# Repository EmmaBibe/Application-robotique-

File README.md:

# RoboMaster

Un parcours complet pour apprendre la robotique en partant de zéro, jusqu'au niveau attendu en Master, et au-delà.

L'idée : on ne mémorise pas une notion avant de l'avoir manipulée. Chaque leçon montre le phénomène de la source jusqu'au résultat (du courant dans un fil jusqu'au robot qui tourne), puis propose des simulateurs à manipuler, des quiz, des exercices corrigés, du code à écrire et des défis.

Fonctionne sur ordinateur et sur téléphone, s'installe comme une application et marche hors connexion. Aucun compte, aucune donnée envoyée : la progression reste sur l'appareil.

## Contenu

- **94 leçons** réparties en **28 modules** et **6 phases** :
  1. *Fondations* : bien démarrer, mathématiques, physique, électronique, programmation
  2. *Le cœur de la robotique* : mécanique et actionneurs, systèmes embarqués, robots mobiles, bras manipulateurs, commande et asservissements
  3. *Le robot intelligent* : perception et capteurs, vision, localisation et SLAM, planification, intelligence artificielle, ROS 2
  4. *L'ingénieur de demain* : ingénierie système et sécurité, créativité et invention, robotique de demain
  5. *Les frontières* : dynamique des robots, équilibre et robots à pattes, drones, essaims et multi-robots, optimisation et commande prédictive, interaction humain-robot, robotique molle et bio-inspirée
  6. *Objectif Mars* : une campagne de 13 missions qui croisent tous les domaines (fusée, trajectoire, atterrissage, énergie, rover, autonomie, terrain, hélicoptère, grottes, construction, ressources locales, dossier final), suivie de 3 ateliers « retour sur Terre » ancrés en RDC
- **29 simulateurs interactifs** : vecteurs, cercle trigonométrique, matrices de transformation, profil de mouvement, masse-ressort, engrenages, loi d'Ohm, PWM et pont en H, conversion analogique-numérique, robot différentiel et odométrie, bras 2 axes (modèles direct et inverse), PID, capteurs de distance (lidar, ultrason, infrarouge), filtrage et Kalman, filtre particulaire, A* et compagnie, convolution d'images, neurone artificiel, Q-learning, suiveur de ligne programmable, graphe ROS 2, dynamique d'un bras (Terre, Mars, Lune), pendule inversé (PID contre LQR), drone sur Terre et sur Mars, essaim d'exploration, transfert Terre-Mars, atterrissage propulsé, rover piloté avec délai radio, budget énergétique martien
- **Ateliers de conception** chiffrés (fusée à deux étages, mobilité d'un rover, énergie d'une base, drone de livraison, robot solaire) et **dossiers d'ingénieur** à questions ouvertes avec grille d'auto-évaluation, gardés dans le carnet
- **52 exercices de code** corrigés automatiquement, des dizaines d'exercices numériques et de quiz
- **Défis** : réglages de PID, choix de résistance, labyrinthe qui piège A*, tour chronométré du suiveur de ligne, et des défis créatifs à réaliser hors de l'écran
- **Révision espacée** (boîtes de Leitner) avec plus de 300 cartes
- **Carnet d'ingénieur** pour noter idées (problème, idée, prototype, test) et réflexions, exportable
- **Projets réels** avec matériel, budget et étapes : veilleuse, suiveur de ligne, bras à servos, gyropode, robot autonome sous ROS 2
- **Guide du Master** : programme type, outils à maîtriser, calendrier conseillé, stage et débouchés
- Glossaire français-anglais, recherche globale, minuteur de concentration, niveaux, badges, série de jours, thème clair et sombre

## Lancer l'application

Aucune dépendance, aucune étape de compilation. Il suffit de servir le dossier avec n'importe quel serveur web statique :

```bash
python3 -m http.server 8000
# puis ouvrir http://localhost:8000
```

Le mode hors ligne et l'installation nécessitent HTTPS (ou `localhost`). Pour publier, GitHub Pages, Netlify ou n'importe quel hébergement statique conviennent.

**Installer sur téléphone** : ouvrir le site, puis « Ajouter à l'écran d'accueil » dans le menu du navigateur.
**Installer sur ordinateur** : icône d'installation dans la barre d'adresse (Chrome, Edge).

**Changer d'appareil** : Profil → Exporter ma progression, puis Importer sur l'autre appareil.

## Organisation du code

```
index.html              coquille de l'application
css/app.css             styles (thème sombre et clair, mobile et bureau)
js/app.js               routeur et pages (accueil, parcours, leçon, labo, révision...)
js/core/                stockage local, gamification, interface, outils de dessin
js/views/blocks.js      rendu des blocs de leçon (quiz, exercices, code, défis...)
js/sims/                un fichier par simulateur, chargé à la demande
js/content/             le contenu pédagogique (un fichier par groupe de modules)
tools/build-sw.mjs      régénère sw.js (liste des fichiers mis en cache hors ligne)
```

### Ajouter ou modifier une leçon

Les leçons sont écrites dans `js/content/m-*.js` avec de petites fonctions (`P`, `H`, `Sim`, `Q`, `Exo`, `Code`, `Defi`...) définies dans `js/content/b.js`. Exemple :

```js
Q('q1', 'Que mesure un codeur ?', ['Une distance', 'Une rotation', 'Une température'], 1, 'Il compte les pas de rotation d\'un axe.'),
Exo('e1', 'Convertis 90° en radians.', { answer: 1.5708, tol: 0.001, sol: 'π/2 ≈ 1,571 rad' }),
Sim('pid', { Kp: 2 }),
```

Après toute modification, régénérer la liste du cache hors ligne :

```bash
node tools/build-sw.mjs
```

## Application Android (APK)

Le dossier `android/` contient une coquille Android minimale qui embarque l'application web et la fait tourner hors connexion. Pour reconstruire l'APK :

```bash
export ANDROID_HOME=/chemin/vers/android-sdk   # avec platforms;android-34 et build-tools;35.0.0
./android/build-apk.sh                         # produit android/RoboMaster.apk
```

Le script n'utilise ni Gradle ni Android Studio : aapt2, javac, d8, zipalign et apksigner suffisent. La clé `android/robomaster.keystore` sert uniquement aux versions de test ; elle est conservée pour que chaque nouvelle APK s'installe par-dessus la précédente sans perdre la progression.

## Application Windows

Le dossier `desktop/` contient une version de bureau basée sur Electron : une fenêtre qui sert l'application embarquée, sans installation ni connexion. Pour la reconstruire :

```bash
./desktop/build-windows.sh   # produit desktop/dist/RoboMaster-Windows.zip
```

Décompresser l'archive puis lancer `RoboMaster.exe`. La progression est enregistrée dans le profil Windows de l'utilisateur.

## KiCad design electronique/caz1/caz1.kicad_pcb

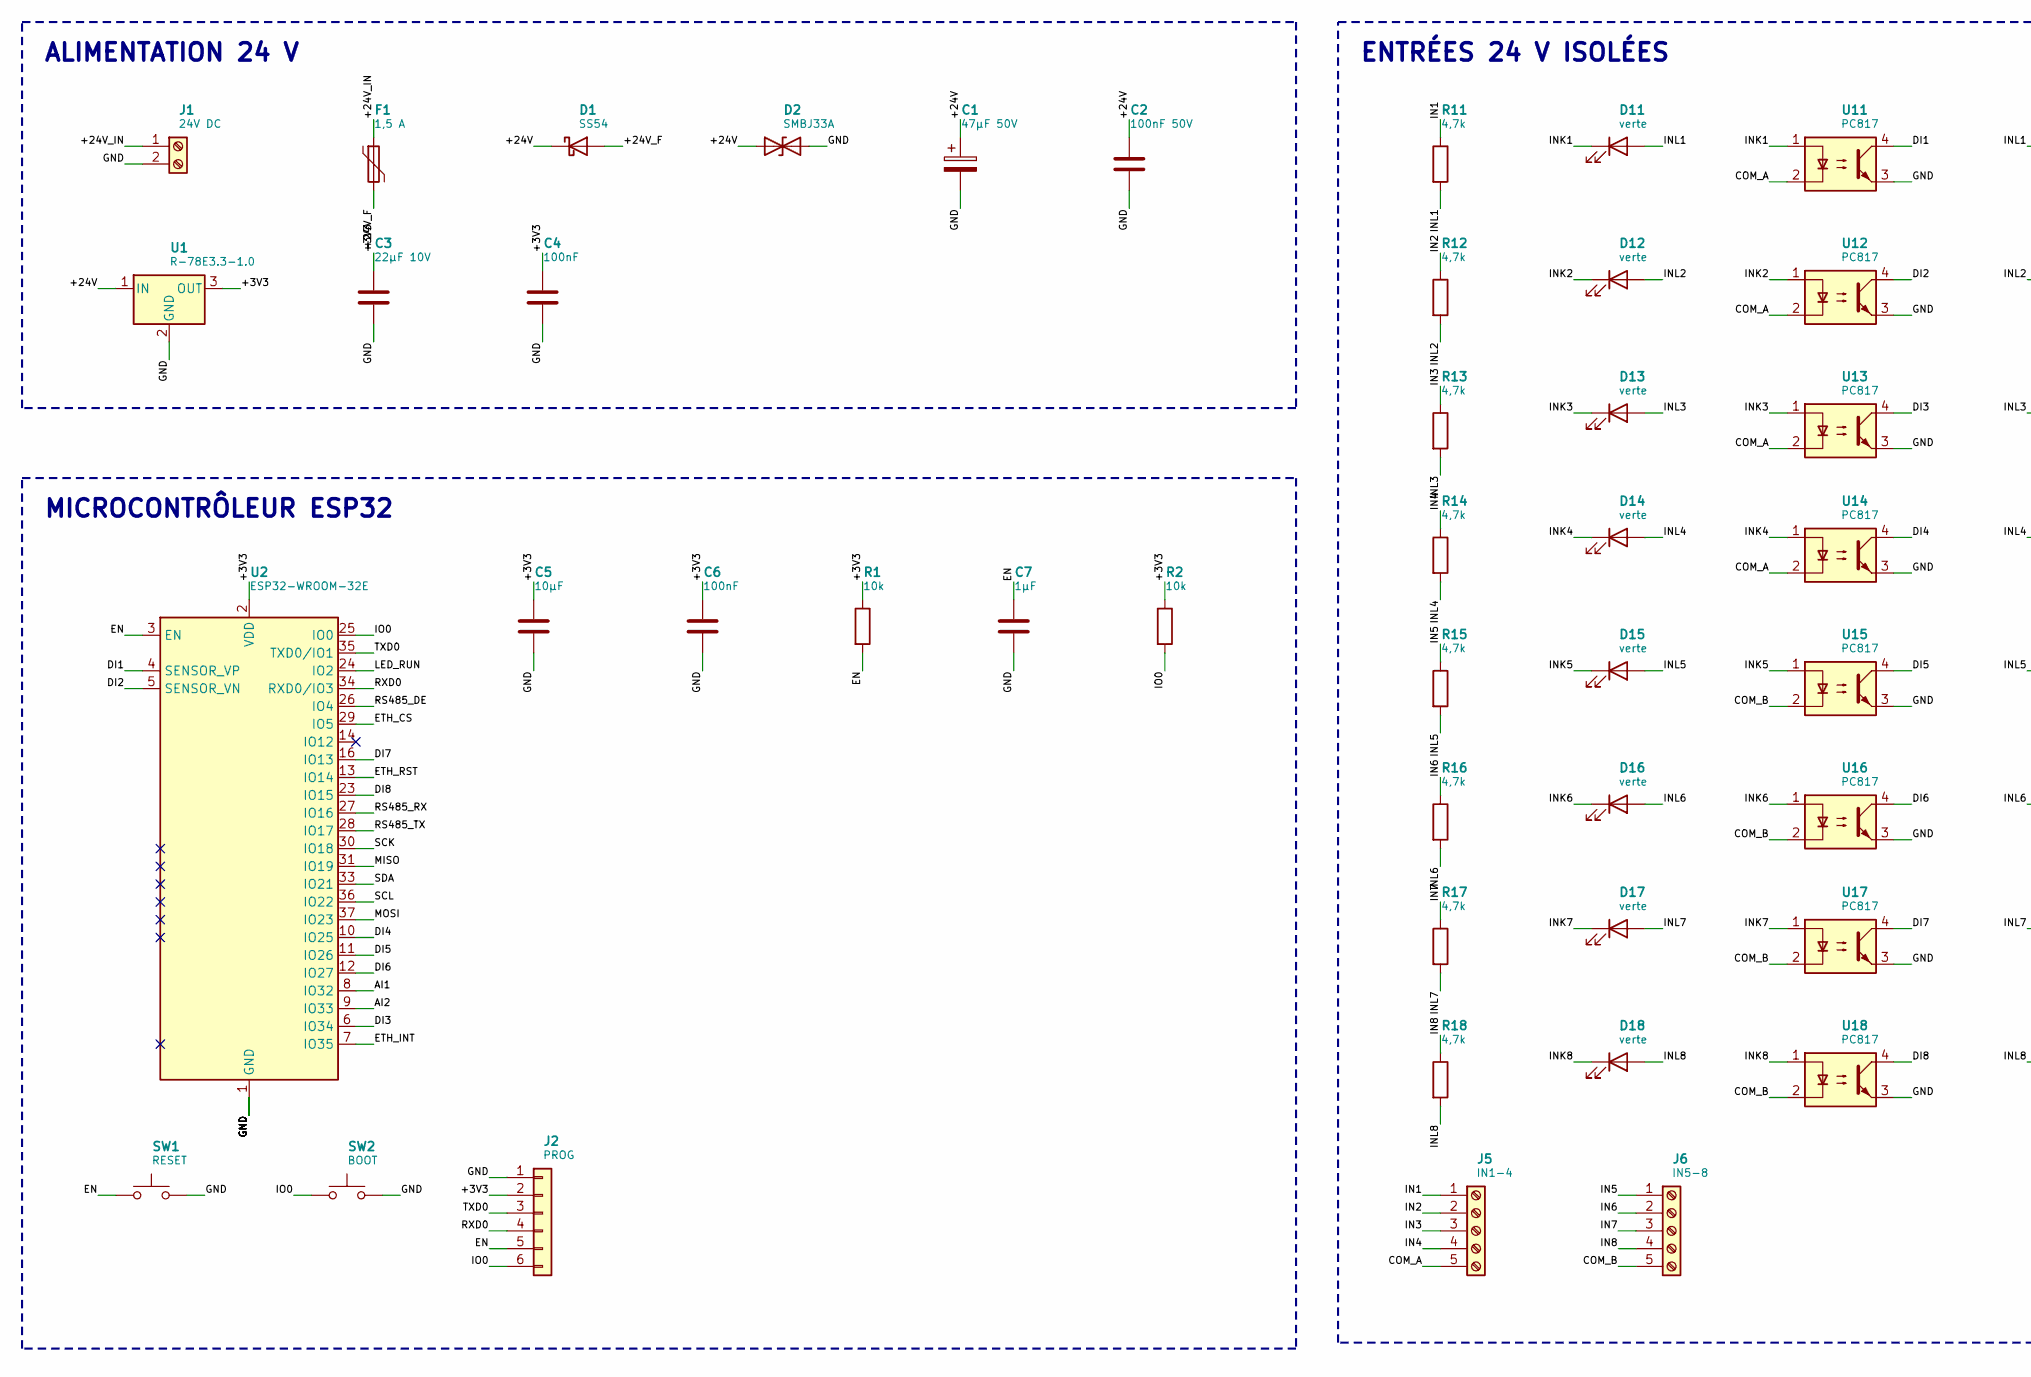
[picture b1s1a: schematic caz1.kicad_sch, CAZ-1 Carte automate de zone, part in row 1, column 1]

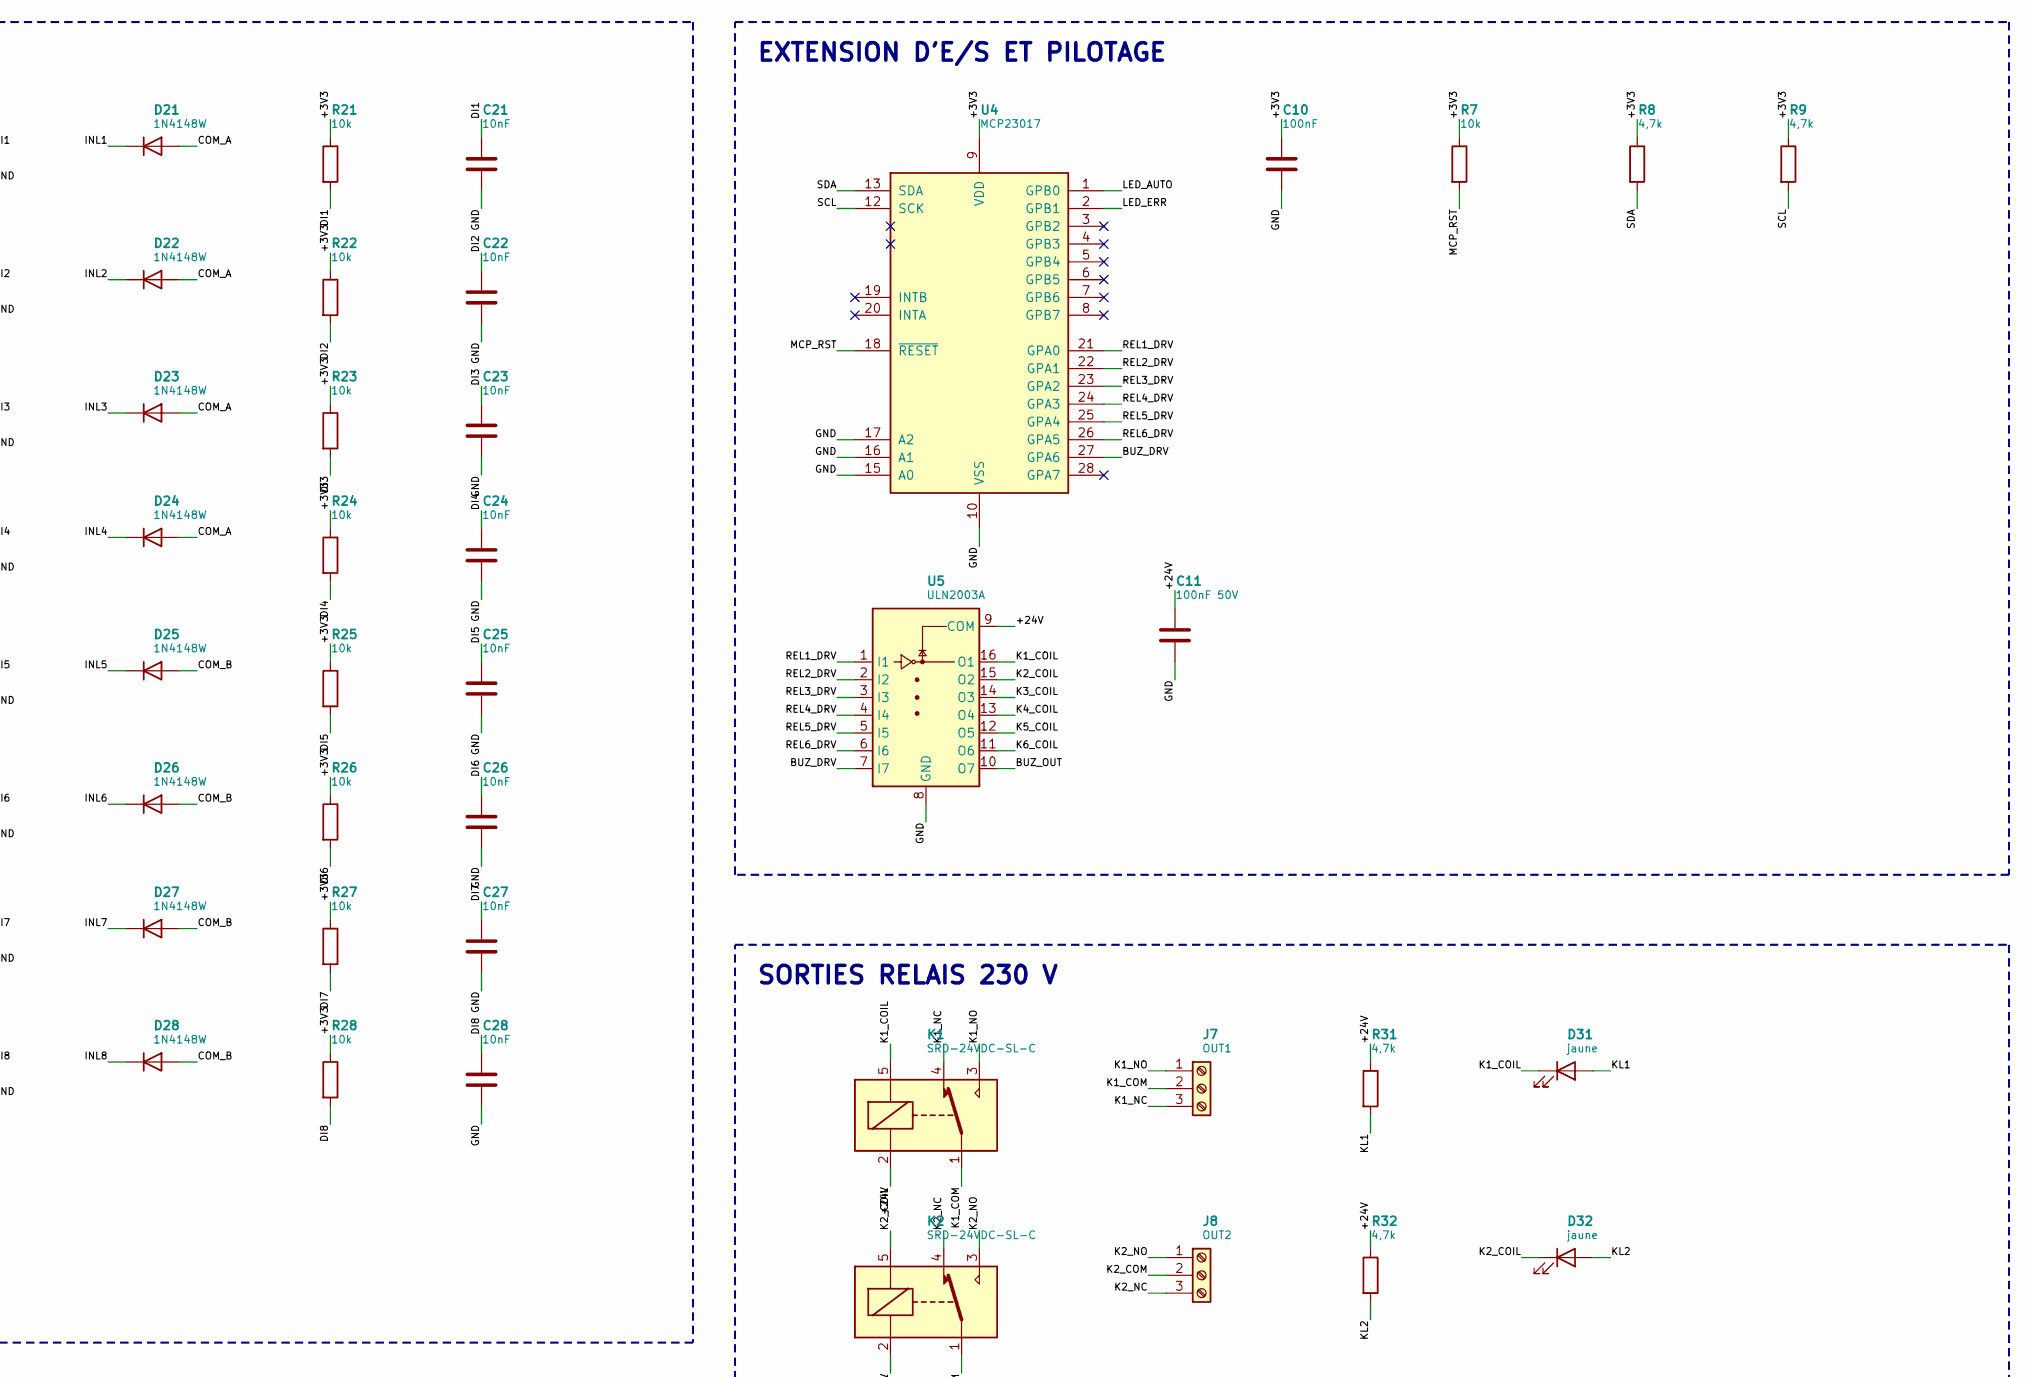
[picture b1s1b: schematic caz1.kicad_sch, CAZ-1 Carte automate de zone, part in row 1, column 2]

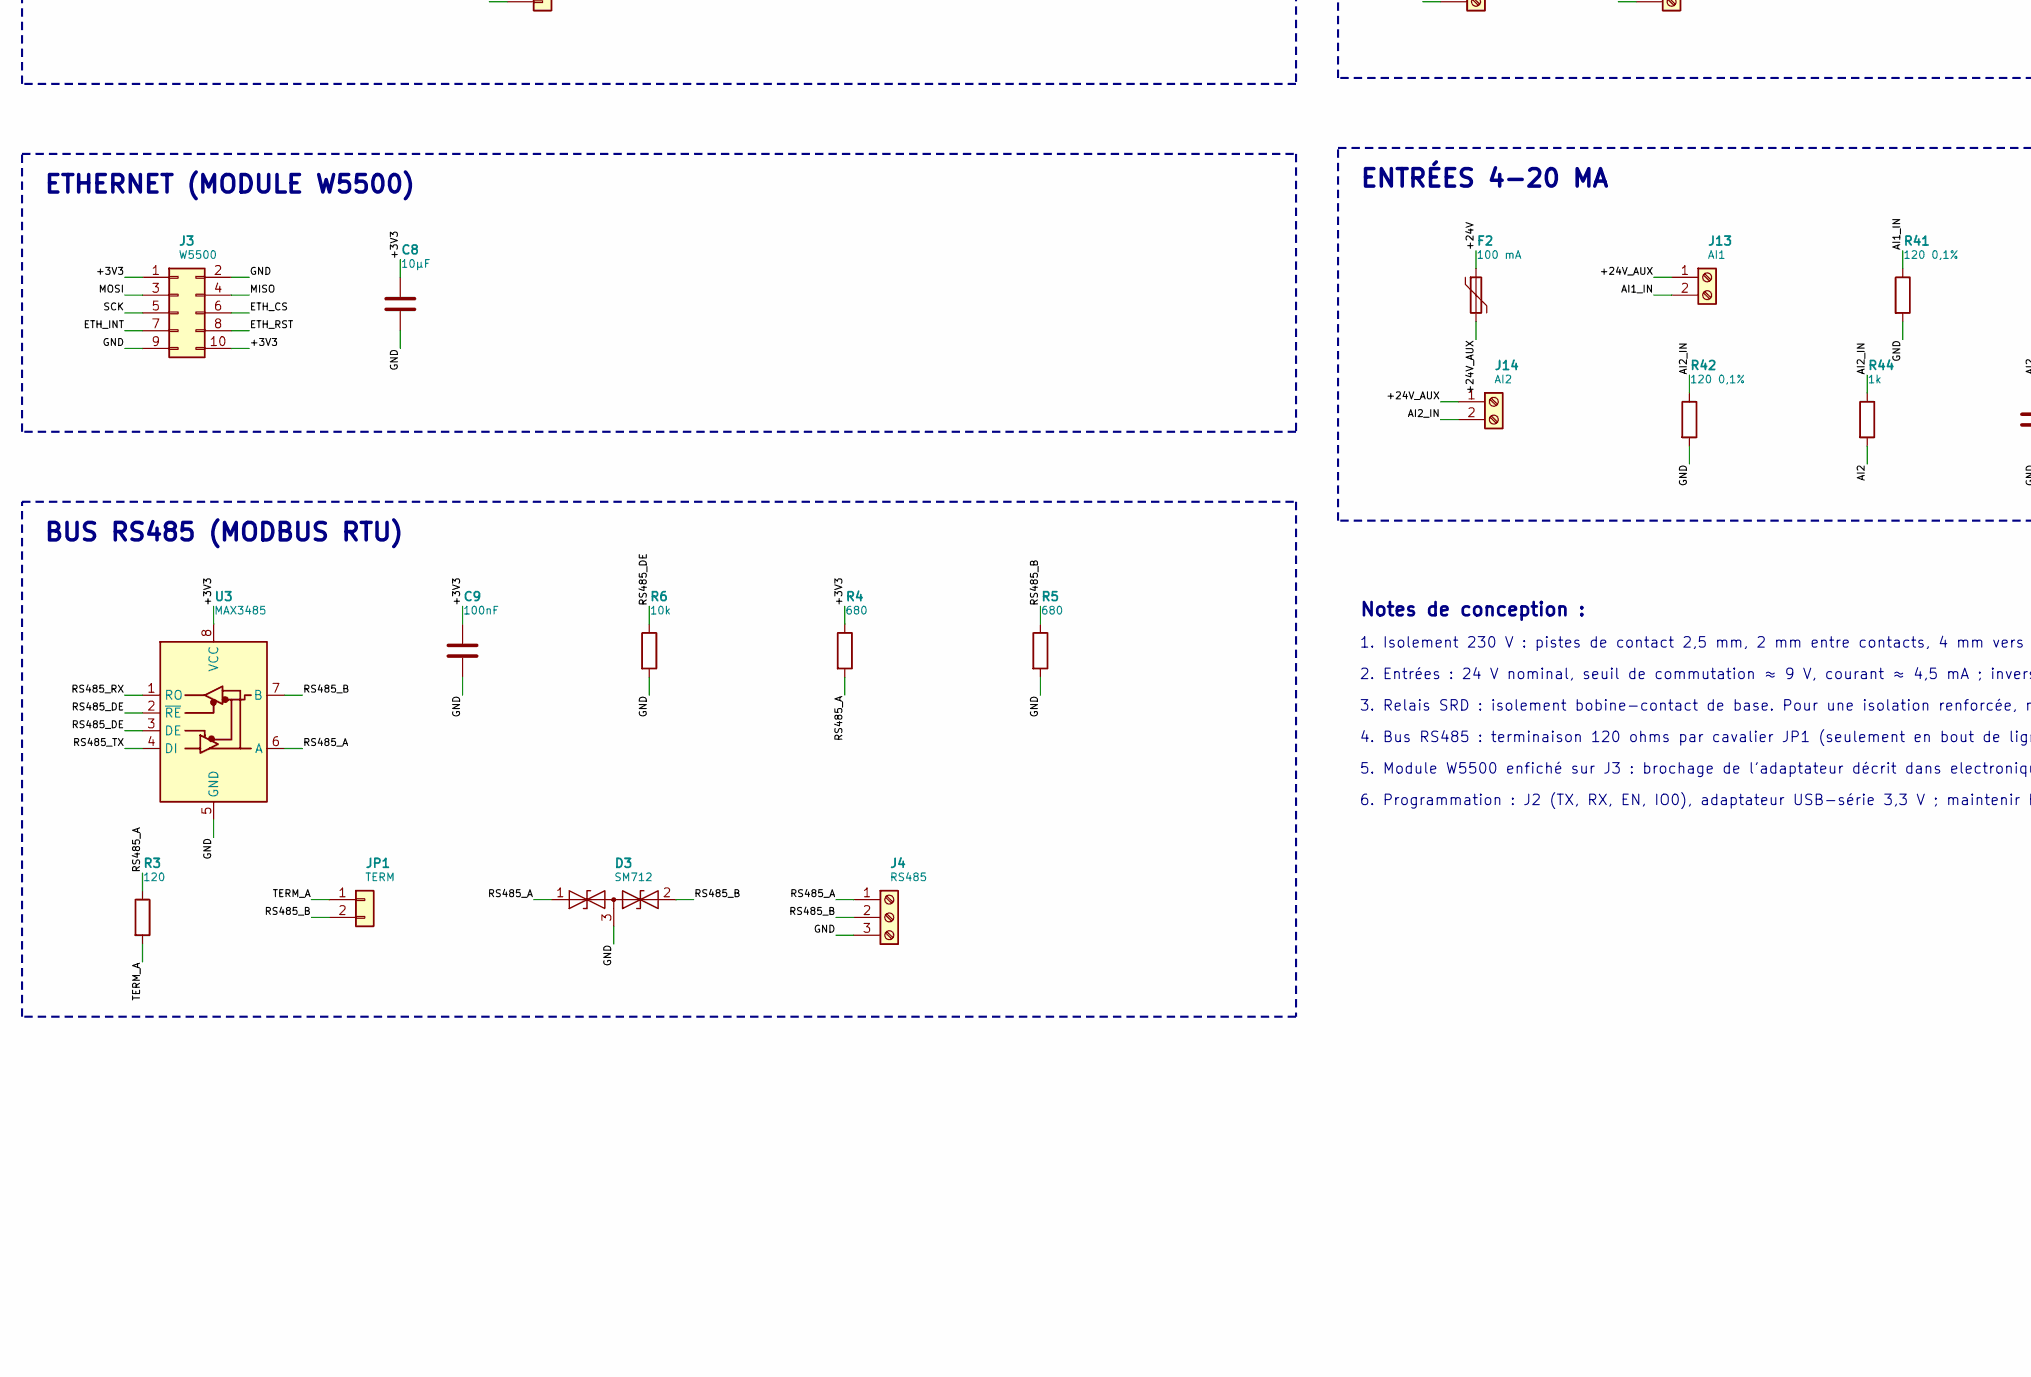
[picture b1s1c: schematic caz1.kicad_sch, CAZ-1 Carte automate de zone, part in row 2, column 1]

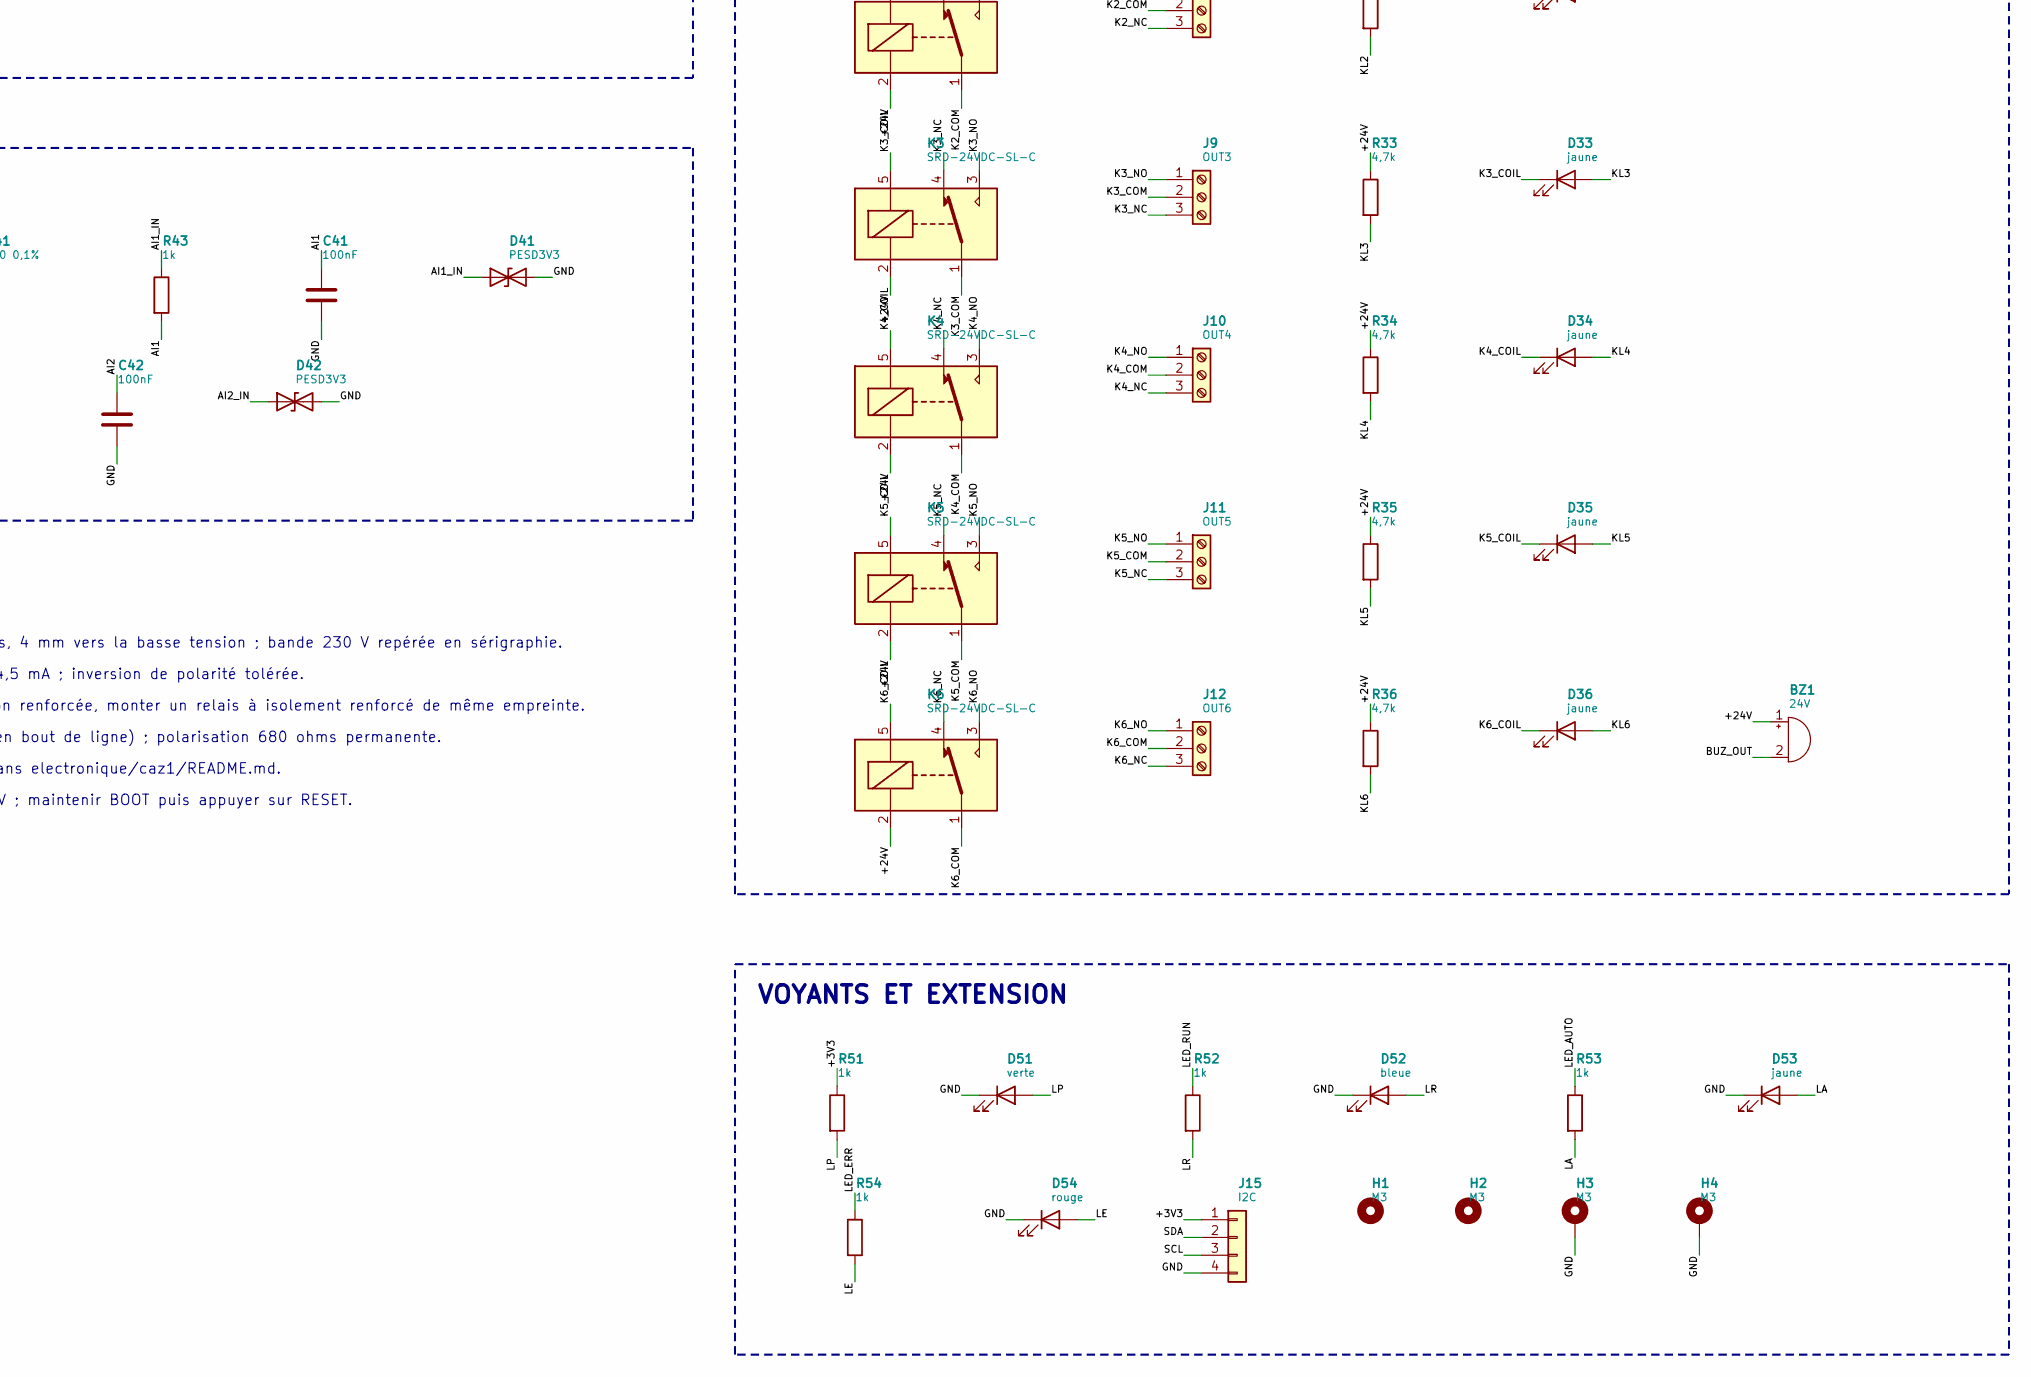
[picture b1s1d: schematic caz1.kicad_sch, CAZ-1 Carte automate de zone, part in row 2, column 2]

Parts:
BZ1: 24V; Buzzer_12x9.5RM7.6
C1: 47µF 50V; CP_Elec_8x10
C2, C11: 100nF 50V; C_0805_2012Metric
C3: 22µF 10V; C_1206_3216Metric
C4, C6, C9, C10, C41, C42: 100nF; C_0603_1608Metric
C5, C8: 10µF; C_0805_2012Metric
C7: 1µF; C_0603_1608Metric
C21, C22, C23, C24, C25, C26, C27, C28: 10nF; C_0603_1608Metric
D1: SS54; D_SMA
D2: SMBJ33A; D_SMB
D3: SM712; SOT-23
D11, D12, D13, D14, D15, D16, D17, D18, D51: verte; LED_0805_2012Metric
D21, D22, D23, D24, D25, D26, D27, D28: 1N4148W; D_SOD-123
D31, D32, D33, D34, D35, D36, D53: jaune; LED_0805_2012Metric
D41, D42: PESD3V3; D_SOD-323
D52: bleue; LED_0805_2012Metric
D54: rouge; LED_0805_2012Metric
F1: 1,5 A; Fuse_1812_4532Metric
F2: 100 mA; Fuse_1206_3216Metric
H1, H2: M3; MountingHole_3.2mm_M3
H3, H4: M3; MountingHole_3.2mm_M3_Pad_Via
J1: 24V DC; TerminalBlock_Phoenix_MKDS-1,5-2-5.08_1x02_P5.08mm_Horizont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
J2: PROG; PinHeader_1x06_P2.54mm_Vertical
J3: W5500; PinSocket_2x05_P2.54mm_Vertical
J4: RS485; TerminalBlock_Phoenix_MKDS-1,5-3-5.08_1x03_P5.08mm_Horizont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
J5: IN1-4; TerminalBlock_Phoenix_MKDS-1,5-5-5.08_1x05_P5.08mm_Horizont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
J6: IN5-8; TerminalBlock_Phoenix_MKDS-1,5-5-5.08_1x05_P5.08mm_Horizont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
J7: OUT1; TerminalBlock_Phoenix_MKDS-1,5-3-5.08_1x03_P5.08mm_Horizont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
J8: OUT2; TerminalBlock_Phoenix_MKDS-1,5-3-5.08_1x03_P5.08mm_Horizont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
J9: OUT3; TerminalBlock_Phoenix_MKDS-1,5-3-5.08_1x03_P5.08mm_Horizont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
J10: OUT4; TerminalBlock_Phoenix_MKDS-1,5-3-5.08_1x03_P5.08mm_Horizont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
J11: OUT5; TerminalBlock_Phoenix_MKDS-1,5-3-5.08_1x03_P5.08mm_Horizont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
J12: OUT6; TerminalBlock_Phoenix_MKDS-1,5-3-5.08_1x03_P5.08mm_Horizont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
J13: AI1; TerminalBlock_Phoenix_MKDS-1,5-2-5.08_1x02_P5.08mm_Horizont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
J14: AI2; TerminalBlock_Phoenix_MKDS-1,5-2-5.08_1x02_P5.08mm_Horizont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
J15: I2C; JST_XH_B4B-XH-A_1x04_P2.50mm_Vertical
JP1: TERM; PinHeader_1x02_P2.54mm_Vertical
K1, K2, K3, K4, K5, K6: SRD-24VDC-SL-C; Relay_SPDT_SANYOU_SRD_Series_Form_C
R1, R2, R6, R7, R21, R22, R23, R24, R25, R26, R27, R28: 10k; R_0805_2012Metric
R3: 120; R_1206_3216Metric
R4, R5: 680; R_0805_2012Metric
R8, R9, R31, R32, R33, R34, R35, R36: 4,7k; R_0805_2012Metric
R11, R12, R13, R14, R15, R16, R17, R18: 4,7k; R_1206_3216Metric
R41, R42: 120 0,1%; R_1206_3216Metric
R43, R44, R51, R52, R53, R54: 1k; R_0805_2012Metric
SW1: RESET; SW_PUSH_6mm
SW2: BOOT; SW_PUSH_6mm
U1: R-78E3.3-1.0; Converter_DCDC_RECOM_R-78E-0.5_THT
U2: ESP32-WROOM-32E; ESP32-WROOM-32D
U3: MAX3485; SOIC-8_3.9x4.9mm_P1.27mm
U4: MCP23017; SOIC-28W_7.5x17.9mm_P1.27mm
U5: ULN2003A; SOIC-16_3.9x9.9mm_P1.27mm
U11, U12, U13, U14, U15, U16, U17, U18: PC817; DIP-4_W7.62mm

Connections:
+3V3: C3.1, C4.1, C5.1, C6.1, C8.1, C9.1, C10.1, J2.2, J3.1, J3.10, J15.1, R1.1, R2.1, R4.1, R7.1, R8.1, R9.1, R21.1, R22.1, R23.1, R24.1, R25.1, R26.1, R27.1, R28.1, R51.1, U1.3 (OUT), U2.2 (VDD), U3.8 (VCC), U4.9 (VDD)
+24V: BZ1.1 (+), C1.1, C2.1, C11.1, D1.1 (K), D2.1 (A1), F2.1, K1.2, K2.2, K3.2, K4.2, K5.2, K6.2, R31.1, R32.1, R33.1, R34.1, R35.1, R36.1, U1.1 (IN), U5.9 (COM)
+24V_AUX: F2.2, J13.1, J14.1
+24V_F: D1.2 (A), F1.2
+24V_IN: F1.1, J1.1
AI1: C41.1, R43.2, U2.8 (IO32)
AI1_IN: D41.1 (A1), J13.2, R41.1, R43.1
AI2: C42.1, R44.2, U2.9 (IO33)
AI2_IN: D42.1 (A1), J14.2, R42.1, R44.1
BUZ_DRV: U4.27 (GPA6), U5.7 (I7)
BUZ_OUT: BZ1.2 (-), U5.10 (O7)
COM_A: D21.2 (A), D22.2 (A), D23.2 (A), D24.2 (A), J5.5, U11.2, U12.2, U13.2, U14.2
COM_B: D25.2 (A), D26.2 (A), D27.2 (A), D28.2 (A), J6.5, U15.2, U16.2, U17.2, U18.2
DI1: C21.1, R21.2, U2.4 (SENSOR_VP), U11.4
DI2: C22.1, R22.2, U2.5 (SENSOR_VN), U12.4
DI3: C23.1, R23.2, U2.6 (IO34), U13.4
DI4: C24.1, R24.2, U2.10 (IO25), U14.4
DI5: C25.1, R25.2, U2.11 (IO26), U15.4
DI6: C26.1, R26.2, U2.12 (IO27), U16.4
DI7: C27.1, R27.2, U2.16 (IO13), U17.4
DI8: C28.1, R28.2, U2.23 (IO15), U18.4
EN: C7.1, J2.5, R1.2, SW1.1, U2.3 (EN)
ETH_CS: J3.6, U2.29 (IO5)
ETH_INT: J3.7, U2.7 (IO35)
ETH_RST: J3.8, U2.13 (IO14)
GND: C1.2, C2.2, C3.2, C4.2, C5.2, C6.2, C7.2, C8.2, C9.2, C10.2, C11.2, C21.2, C22.2, C23.2, C24.2, C25.2, C26.2, C27.2, C28.2, C41.2, C42.2, D2.2 (A2), D3.3 (common), D41.2 (A2), D42.2 (A2), D51.1 (K), D52.1 (K), D53.1 (K), D54.1 (K), H3.1, H4.1, J1.2, J2.1, J3.2, J3.9, J4.3, J15.4, R5.2, R6.2, R41.2, R42.2, SW1.2, SW2.2, U1.2 (GND), U2.1 (GND), U2.15 (GND), U2.38 (GND), U2.39 (GND), U3.5 (GND), U4.10 (VSS), U4.15 (A0), U4.16 (A1), U4.17 (A2), U5.8 (GND), U11.3, U12.3, U13.3, U14.3, U15.3, U16.3, U17.3, U18.3
IN1: J5.1, R11.1
IN2: J5.2, R12.1
IN3: J5.3, R13.1
IN4: J5.4, R14.1
IN5: J6.1, R15.1
IN6: J6.2, R16.1
IN7: J6.3, R17.1
IN8: J6.4, R18.1
INK1: D11.1 (K), U11.1
INK2: D12.1 (K), U12.1
INK3: D13.1 (K), U13.1
INK4: D14.1 (K), U14.1
INK5: D15.1 (K), U15.1
INK6: D16.1 (K), U16.1
INK7: D17.1 (K), U17.1
INK8: D18.1 (K), U18.1
INL1: D11.2 (A), D21.1 (K), R11.2
INL2: D12.2 (A), D22.1 (K), R12.2
INL3: D13.2 (A), D23.1 (K), R13.2
INL4: D14.2 (A), D24.1 (K), R14.2
INL5: D15.2 (A), D25.1 (K), R15.2
INL6: D16.2 (A), D26.1 (K), R16.2
INL7: D17.2 (A), D27.1 (K), R17.2
INL8: D18.2 (A), D28.1 (K), R18.2
IO0: J2.6, R2.2, SW2.1, U2.25 (IO0)
K1_COIL: D31.1 (K), K1.5, U5.16 (O1)
K1_COM: J7.2, K1.1
K1_NC: J7.3, K1.4
K1_NO: J7.1, K1.3
K2_COIL: D32.1 (K), K2.5, U5.15 (O2)
K2_COM: J8.2, K2.1
K2_NC: J8.3, K2.4
K2_NO: J8.1, K2.3
K3_COIL: D33.1 (K), K3.5, U5.14 (O3)
K3_COM: J9.2, K3.1
K3_NC: J9.3, K3.4
K3_NO: J9.1, K3.3
K4_COIL: D34.1 (K), K4.5, U5.13 (O4)
K4_COM: J10.2, K4.1
K4_NC: J10.3, K4.4
K4_NO: J10.1, K4.3
K5_COIL: D35.1 (K), K5.5, U5.12 (O5)
K5_COM: J11.2, K5.1
K5_NC: J11.3, K5.4
K5_NO: J11.1, K5.3
K6_COIL: D36.1 (K), K6.5, U5.11 (O6)
K6_COM: J12.2, K6.1
K6_NC: J12.3, K6.4
K6_NO: J12.1, K6.3
KL1: D31.2 (A), R31.2
KL2: D32.2 (A), R32.2
KL3: D33.2 (A), R33.2
KL4: D34.2 (A), R34.2
KL5: D35.2 (A), R35.2
KL6: D36.2 (A), R36.2
LA: D53.2 (A), R53.2
LE: D54.2 (A), R54.2
LED_AUTO: R53.1, U4.1 (GPB0)
LED_ERR: R54.1, U4.2 (GPB1)
LED_RUN: R52.1, U2.24 (IO2)
LP: D51.2 (A), R51.2
LR: D52.2 (A), R52.2
MCP_RST: R7.2, U4.18 (~RESET)
MISO: J3.4, U2.31 (IO19)
MOSI: J3.3, U2.37 (IO23)
REL1_DRV: U4.21 (GPA0), U5.1 (I1)
REL2_DRV: U4.22 (GPA1), U5.2 (I2)
REL3_DRV: U4.23 (GPA2), U5.3 (I3)
REL4_DRV: U4.24 (GPA3), U5.4 (I4)
REL5_DRV: U4.25 (GPA4), U5.5 (I5)
REL6_DRV: U4.26 (GPA5), U5.6 (I6)
RS485_A: D3.1 (A1), J4.1, R3.1, R4.2, U3.6 (A)
RS485_B: D3.2 (A2), J4.2, JP1.2, R5.1, U3.7 (B)
RS485_DE: R6.1, U2.26 (IO4), U3.2 (~RE), U3.3 (DE)
RS485_RX: U2.27 (IO16), U3.1 (RO)
RS485_TX: U2.28 (IO17), U3.4 (DI)
RXD0: J2.4, U2.34 (RXD0/IO3)
SCK: J3.5, U2.30 (IO18)
SCL: J15.3, R9.2, U2.36 (IO22), U4.12 (SCK)
SDA: J15.2, R8.2, U2.33 (IO21), U4.13 (SDA)
TERM_A: JP1.1, R3.2
TXD0: J2.3, U2.35 (TXD0/IO1)

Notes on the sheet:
ALIMENTATION 24 V
MICROCONTRÔLEUR ESP32
ETHERNET (MODULE W5500)
BUS RS485 (MODBUS RTU)
ENTRÉES 24 V ISOLÉES
EXTENSION D'E/S ET PILOTAGE
SORTIES RELAIS 230 V
ENTRÉES 4-20 MA
VOYANTS ET EXTENSION
Notes de conception :
1. Isolement 230 V : pistes de contact 2,5 mm, 2 mm entre contacts, 4 mm vers la basse tension ; bande 230 V repérée en sérigraphie.
2. Entrées : 24 V nominal, seuil de commutation ≈ 9 V, courant ≈ 4,5 mA ; inversion de polarité tolérée.
3. Relais SRD : isolement bobine-contact de base. Pour une isolation renforcée, monter un relais à isolement renforcé de même empreinte.
4. Bus RS485 : terminaison 120 ohms par cavalier JP1 (seulement en bout de ligne) ; polarisation 680 ohms permanente.
5. Module W5500 enfiché sur J3 : brochage de l'adaptateur décrit dans electronique/caz1/README.md.
6. Programmation : J2 (TX, RX, EN, IO0), adaptateur USB-série 3,3 V ; maintenir BOOT puis appuyer sur RESET.

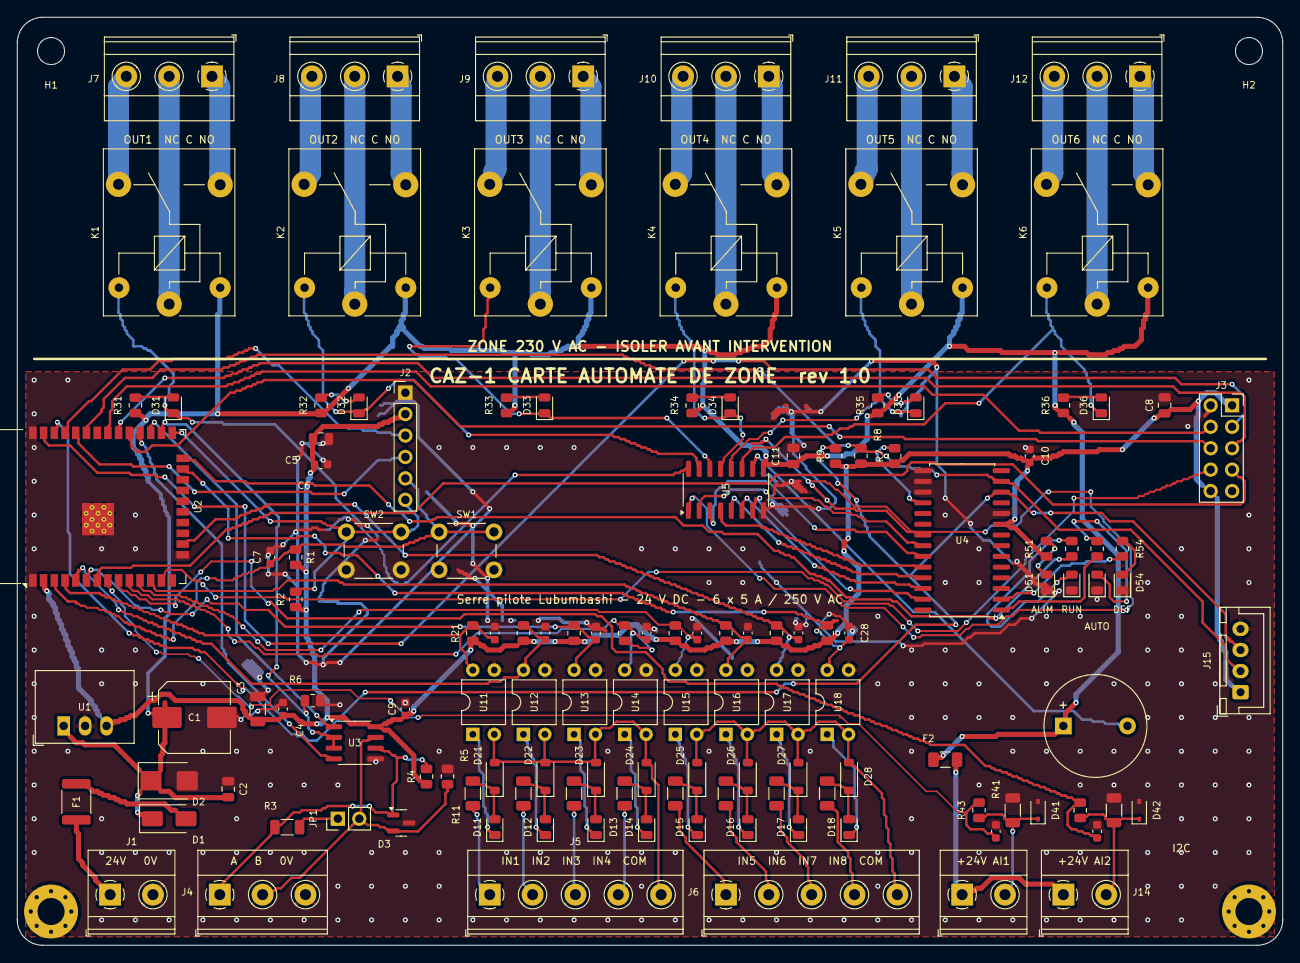
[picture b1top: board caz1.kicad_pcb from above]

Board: 2 copper layers, 150.0 x 110.0 mm, 135 parts (0 on the bottom side), 108 nets.

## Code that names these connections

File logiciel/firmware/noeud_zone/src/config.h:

// Configuration matérielle et réglages de repli. À adapter au câblage réel
// de chaque armoire (voir le schéma de l'armoire de zone).
#pragma once

#define SITE "serre/lub1"

// --- réseau (les identifiants réels ne sont jamais versionnés : fichier secrets.h)
#if __has_include("secrets.h")
#include "secrets.h"
#else
#define MQTT_SERVEUR "192.168.10.2"
#define MQTT_UTILISATEUR "aut-" ZONE
#define MQTT_MOT_DE_PASSE "a-changer"
#endif

// --- bus RS485 (Modbus RTU, 9600 bauds 8N1). Les autres broches de la carte
// sont prises par l'interface Ethernet.
#define PIN_RS485_RX 36
#define PIN_RS485_TX 4
#define PIN_RS485_DE 5
#define PIN_VOYANT_AUTONOME 2

// --- adresses Modbus
#define ADR_TH   1   // température / humidité sous abri ventilé
#define ADR_CO2  2
#define ADR_EC   3
#define ADR_PH   4
#define ADR_TSOL 5
#define ADR_O2   6   // feuilles uniquement
#define ADR_TSTO 7   // fruits uniquement : cuve de stockage thermique
#define ADR_ES   10  // module 16 relais / 16 entrées

// --- canaux de sortie du module d'E/S (relais)
#define Q_OUV_OUVRE        0
#define Q_OUV_FERME        1
#define Q_ECR_OUVRE        2
#define Q_ECR_FERME        3
#define Q_PAD              4
#define Q_EXTRACTEUR_V1    5
#define Q_EXTRACTEUR_V2    6
#define Q_BRASSAGE         7
#define Q_STOCKAGE         8
#define Q_CO2              9   // fruits
#define Q_AERATION_BASSINS_ARRET 9   // feuilles : relais à ouverture, repos = surpresseur en marche

// --- canaux d'entrée du module d'E/S (contacts secs)
#define IN_OUV_FIN_O    0
#define IN_OUV_FIN_F    1
#define IN_ECR_FIN_O    2
#define IN_ECR_FIN_F    3
#define IN_ANEMO_ALARME 4

// --- mécanique
#define DUREE_COURSE_OUVRANT_S 180.0f
#define DUREE_COURSE_ECRAN_S   240.0f

// --- sécurité et repli
#define VENT_LIMITE     10.0f
#define VENT_FERMETURE  14.0f
#ifdef ZONE_FRUITS
#define T_AERATION_REPLI  25.0f
#define T_CHAUFFAGE_REPLI 15.0f
#else
#define T_AERATION_REPLI  23.0f
#define T_CHAUFFAGE_REPLI 12.0f
#endif
